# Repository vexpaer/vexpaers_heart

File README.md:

# vexpaer's heart — clean PCB rebuild

This branch resets the PCB layout workflow without losing the previous design.

- `Old/`: complete archived V1 design and production outputs.
- `reference/`: only the electrical/spec/library files needed for the rebuild.
- `hardware/heart_v2/`: clean workspace for the new PCB.
- `PCB_WORKFLOW.md`: the one document Codex should follow from setup to final manufacturing outputs.

The new PCB must be placement-first and human-routed. Do not use the archived PCB tracks or a global autorouter as the final layout.

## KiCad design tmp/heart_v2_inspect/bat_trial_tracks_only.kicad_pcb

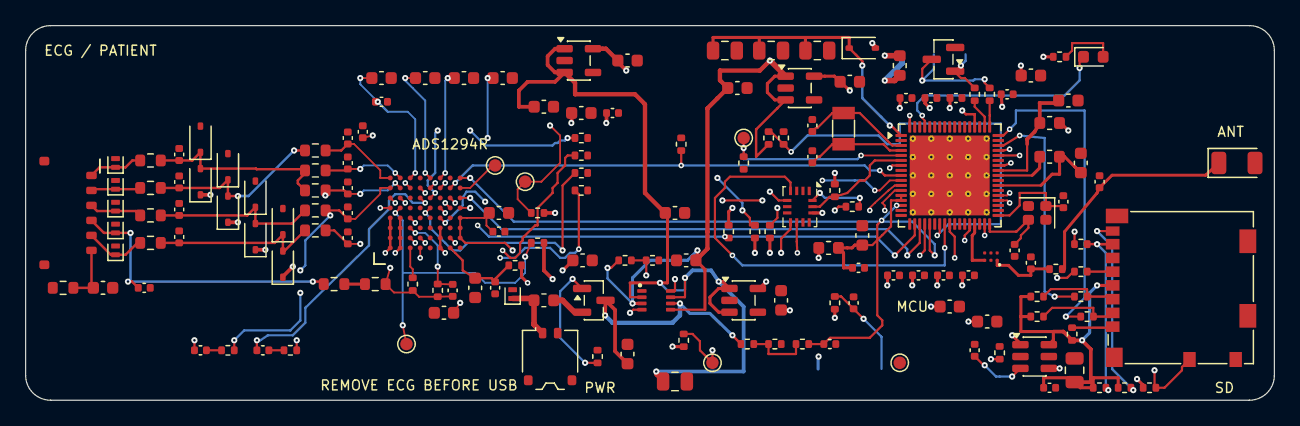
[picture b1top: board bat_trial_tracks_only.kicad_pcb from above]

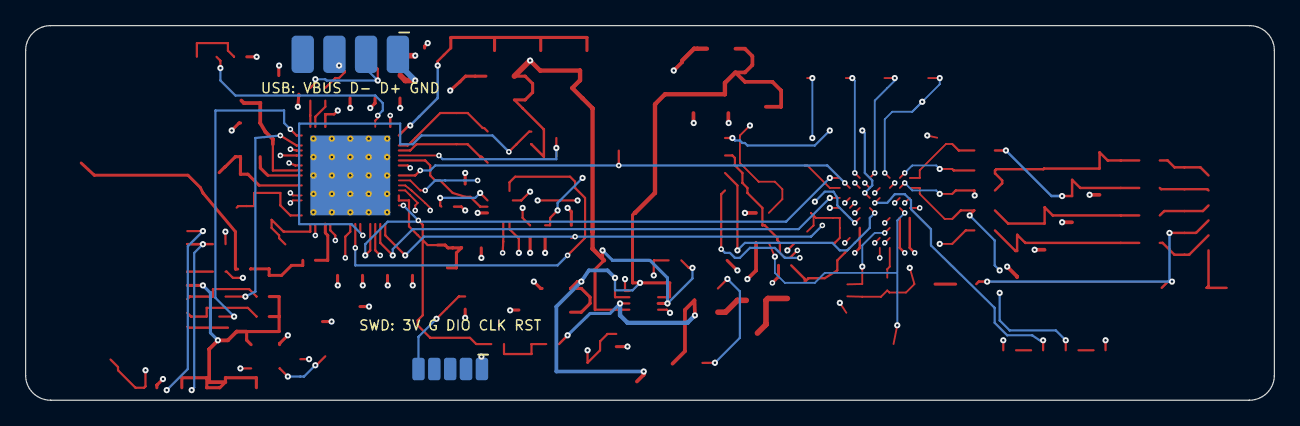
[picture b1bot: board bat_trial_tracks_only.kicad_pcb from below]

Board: 4 copper layers, 100.0 x 30.0 mm, 167 parts (2 on the bottom side), 102 nets.

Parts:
AE1: 2450AT18A100E; Johanson_2450AT18x100_2400-2500Mhz
C1, C2, C3, C4, C5, C6, C7, C8, C9, C13: 100p C0G; C_0402_1005Metric
C10: 100p C0G DNP; C_0402_1005Metric
C11: 1nF 100V C0G; C_0603_1608Metric
C12: 1.5nF C0G; C_0402_1005Metric
C14, C28, C33, C35: 10u 6.3V X5R; C_0603_1608Metric
C15, C21, C23, C25, C38, C48, C50, C51, C52, C53, C54, C55, C56, C58, C59, C64: 100n X7R; C_0402_1005Metric
C16: 22u 6.3V X5R; C_0603_1608Metric
C17, C18, C19, C20, C22, C24, C29, C30, C32, C34, C36, C49, C60, C62: 1u X7R; C_0603_1608Metric
C26, C27: 2.2n C0G DNP; C_0402_1005Metric
C31, C63: 22u 6.3V X5R; C_0805_2012Metric
C37, C46, C47, C57: 4.7u X7R; C_0603_1608Metric
C39, C40, C41: 47u 6.3V X5R; C_0805_2012Metric
C42, C43: 8.2p C0G; C_0402_1005Metric
C44, C45: 10p C0G; C_0402_1005Metric
C61: 1n X7R; C_0402_1005Metric
C65, C66: DNP; C_0402_1005Metric
D1, D2, D3, D4, D5, D14: PESD5V0U1UL; D_SOD-882
D6, D7, D8, D9, D10, D11, D12, D13: BAS116; D_SOD-323
D15: BAT54H; D_SOD-323
D16: GREEN 0603; LED_0603_1608Metric
F1, F2: 0.50A PTC; Fuse_0603_1608Metric
FB1: 600R@100MHz; L_0603_1608Metric
J1: ECG_HARNESS; Molex_Pico-EZmate_78171-5006
J2: PROTECTED_1S_LIPO; Molex_Pico-EZmate_78171-0002_1x02-1MP_P1.20mm_Vertical
J3: USB_POGO; Pogo_USB_4x1_P2.54_Bottom
J4: MICROSD; microSD_HC_Molex_104031-0811
J5: SWD_POGO; Pogo_SWD_5x1_P1.27_Bottom
L1: 10nH; L_0603_1608Metric
L2: 2.2uH; L_0603_1608Metric
Q1: DMP2035U; SOT-23
R1, R2, R3, R4, R5, R6, R7, R8, R9: 47.5k 0.1%; R_0603_1608Metric
R10, R11: 162k 0.1%; R_0603_1608Metric
R12: 1M; R_0603_1608Metric
R13, R15, R16, R17, R51, R52, R53, R54, R55: 0R; R_0402_1005Metric
R14, R20, R26: 1M; R_0402_1005Metric
R18, R19: 40.2k 0.1% DNP; R_0402_1005Metric
R21, R22, R41, R42, R43, R44: 22R; R_0402_1005Metric
R23: 300k; R_0402_1005Metric
R24, R25, R29, R30, R31, R32, R33, R34, R40, R50: 100k; R_0402_1005Metric
R27: 330k; R_0402_1005Metric
R28: 1k; R_0402_1005Metric
R35: 470k; R_0402_1005Metric
R36: 680k; R_0402_1005Metric
R37: 2.2k; R_0402_1005Metric
R38, R39: 4.7k; R_0402_1005Metric
R45, R46, R47, R48, R49: 47k; R_0402_1005Metric
TP1: CH4P; TestPoint_Pad_D1.0mm
TP2: CH4N; TestPoint_Pad_D1.0mm
TP3: BOOT0; TestPoint_Pad_D1.0mm
TP4: PWR_USB_N; TestPoint_Pad_D1.0mm
TP5: ADS_CLK; TestPoint_Pad_D1.0mm
TP6: SWO; TestPoint_Pad_D1.0mm
U1: ADS1294RIZXGT; ADS1294R_ZXG
U2: STM32WB55RGV6; QFN-68-1EP_8x8mm_P0.4mm_EP6.4x6.4mm_ThermalVias
U3: BMI270; Bosch_LGA-14_3x2.5mm_P0.5mm
U4: TPS2116DRLR; Texas_DRL0008A
U5: TPS7A2130PDBVR; SOT-23-5
U6: TPS7A2030PDBVR; SOT-23-5
U7: TPS7A2033PDBVR; SOT-23-5
U8: TPS22918DBVR; SOT-23-6
U9: MLPF-WB55-01E3
U10: TPD2EUSB30DRTR; SOT-23
Y1: 32MHz 6pF; Crystal_SMD_2016-4Pin_2.0x1.6mm
Y2: 32.768kHz 7pF; Crystal_SMD_3215-2Pin_3.2x1.5mm

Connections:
/3V0_A: C20.1, C21.1, C35.1, D6.1 (K), D8.1 (K), D10.1 (K), D12.1 (K), R15.1, R16.2, R17.2, U1.A1 (IN8P), U1.A2 (IN8N), U1.A4 (AVDD), U1.A6 (AVDD), U1.B1 (IN7P), U1.B2 (IN7N), U1.B4 (AVDD), U1.B6 (AVDD), U1.C1 (IN6P), U1.C2 (IN6N), U1.C6 (AVDD), U1.D1 (IN5P), U1.D2 (IN5N), U6.5 (OUT)
/3V0_D: C24.1, C25.1, C33.1, C51.1, C52.1, C53.1, C54.1, C55.1, C57.1, C58.1, C59.1, C60.1, C62.1, D15.2 (A), FB1.1, J5.1 (3V0_D), L1.1, R25.1, R29.1, R30.1, R32.1, R33.1, R37.1, R38.1, R39.1, R50.1, U1.B8 (CLKSEL), U1.C8 (DVDD), U1.D8 (DVDD), U2.30 (VDD), U2.33 (VDDRF), U2.45 (VDD), U2.68 (VDD), U3.5 (VDDIO), U3.8 (VDD), U3.12 (CSB), U5.5 (OUT), U8.1 (VIN)
/3V0_SD: C63.1, C64.1, J4.4 (VDD), R45.1, R46.1, R47.1, R48.1, R49.1, U8.6 (VOUT)
/3V3_USB: C37.1, C56.1, U2.55 (VDDUSB), U7.5 (OUT)
/ADS_AVDD1: C22.1, C23.1, R15.2, U1.A7 (AVDD1)
/ADS_CH1N: C2.1, R2.2, U1.H2 (IN1N)
/ADS_CH1P: C5.1, R5.2, U1.H1 (IN1P)
/ADS_CH2N: C3.1, R3.2, R19.2, U1.G2 (IN2N)
/ADS_CH2P: C7.1, R7.2, R18.2, U1.G1 (IN2P)
/ADS_CH3P: C9.1, R9.2, U1.F1 (IN3P)
/ADS_CH4N: R17.1, TP2.1 (1_1), U1.E2 (IN4N)
/ADS_CH4P: R16.1, TP1.1 (1_1), U1.E1 (IN4P)
/ADS_CLK: TP5.1 (1_1), U1.G8 (CLK)
/ADS_CS: R32.2, U1.F7 (CS), U2.19 (PA4)
/ADS_DRDY: U1.D6 (DRDY), U2.10 (PC1)
/ADS_GPIO1_TIE: R52.1, U1.F5 (GPIO1)
/ADS_GPIO2_TIE: R53.1, U1.E7 (GPIO2)
/ADS_GPIO3_TIE: R54.1, U1.E6 (GPIO3)
/ADS_GPIO4_TIE: R55.1, U1.E5 (GPIO4)
/ADS_MISO: U1.E8 (DOUT), U2.21 (PA6)
/ADS_MOSI: U1.H8 (DIN), U2.22 (PA7)
/ADS_PWDN: R29.2, U1.G5 (PWDN), U2.38 (PB0)
/ADS_RESET: R30.2, U1.G6 (RESET), U2.39 (PB1)
/ADS_RESP_MODN: C27.1, U1.F4 (RESP_MODN)
/ADS_RESP_MODP: C26.1, U1.G4 (RESP_MODP)
/ADS_RLDIN: R13.2, U1.A3 (RLDIN)
/ADS_RLDINV: C12.2, R14.2, U1.C3 (RLDINV)
/ADS_RLDOUT: C12.1, R10.1, R13.1, R14.1, U1.B3 (RLDOUT)
/ADS_SCLK: U1.F8 (SCLK), U2.20 (PA5)
/ADS_START: R31.1, U1.G7 (START), U2.9 (PC0)
/ADS_VCAP1: C16.1, U1.H5 (VCAP1)
/ADS_VCAP2: C17.1, U1.H6 (VCAP2)
/ADS_VCAP3: C18.1, U1.B7 (VCAP3)
/ADS_VCAP4: C19.1, U1.G3 (VCAP4)
/ADS_VREFP: C14.1, C15.1, U1.H3 (VREFP)
/ADS_WCT: C13.1, U1.D3 (WCT), U1.F2 (IN3N)
/BAT_ADC: C38.1, R28.2, U2.15 (PA0)
/BAT_FUSED: F1.2, Q1.2 (S)
/BAT_GATE: Q1.1 (G), R20.1
/BAT_PROT: C28.1, C30.1, Q1.3 (D), R26.1, U4.6 (VIN2)
/BAT_RAW: D14.1, F1.1, J2.1 (BAT+)
/BAT_SENSE_DIV: R26.2, R27.1, R28.1
/BOOT0: R34.1, TP3.1 (1_1), U2.5 (PH3-BOOT0)
/CABLE_SHIELD: C11.1, J1.6 (SHIELD), R12.1
/GND: C1.2, C2.2, C3.2, C4.2, C5.2, C6.2, C7.2, C8.2, C9.2, C10.2, C11.2, C13.2, C14.2, C15.2, C16.2, C17.2, C18.2, C19.2, C20.2, C21.2, C22.2, C23.2, C24.2, C25.2, C28.2, C29.2, C30.2, C31.2, C32.2, C33.2, C34.2, C35.2, C36.2, C37.2, C38.2, C39.2, C40.2, C41.2, C42.2, C43.2, C44.2, C45.2, C46.2, C47.2, C48.2, C49.2, C50.2, C51.2, C52.2, C53.2, C54.2, C55.2, C56.2, C57.2, C58.2, C59.2, C60.2, C61.2, C62.2, C63.2, C64.2, C65.2, C66.2, D1.2, D2.2, D3.2, D4.2, D5.2, D7.2 (A), D9.2 (A), D11.2 (A), D13.2 (A), D14.2, J2.2 (GND), J3.4 (GND), J4.6 (VSS), J4.10 (DET_B), J4.SH (SHIELD), J5.2 (GND), R12.2, R20.2, R24.2, R27.2, R31.2, R34.2, R36.2, R40.2, R52.2, R53.2, R54.2, R55.2, U1.A5 (AVSS), U1.A8 (AVSS1), U1.B5 (AVSS), U1.C5 (AVSS), U1.C7 (DGND), U1.D4 (AVSS), U1.D5 (AVSS), U1.D7 (DGND), U1.E4 (RESV1), U1.F6 (DAISY_IN), U1.H4 (VREFN), U1.H7 (DGND), U2.32 (VSSRF), U2.42 (VSSSMPS), U2.69 (VSS_EP), U3.1 (SDO/ADDR), U3.6 (GNDIO), U3.7 (GND), U4.1 (GND), U5.2 (GND), U6.2 (GND), U7.2 (GND), U8.2 (GND), U8.5 (QOD), U9.A2 (GND), U9.B1 (GND), U9.B2 (GND), U9.B3 (GND), U10.2 (GND), Y1.2 (GND1), Y1.4 (GND2)
/HSE_IN: C42.1, U2.35 (OSC_IN), Y1.1 (X1)
/HSE_OUT: C43.1, U2.34 (OSC_OUT), Y1.3 (X2)
/IMU_INT1: U2.25 (PC4), U3.4 (INT1)
/IMU_INT2: U2.26 (PC5), U3.9 (INT2)
/IMU_SCL: R38.2, U2.6 (PB8), U3.13 (SCx/SCL)
/IMU_SDA: R39.2, U2.7 (PB9), U3.14 (SDx/SDA)
/LA_ELEC: D2.1, J1.2 (LA), R4.1
/LA_PROT: C4.1, D8.2 (A), D9.1 (K), R4.2, R5.1
/LED_STATUS_A: D16.2 (A), R37.2
/LED_STATUS_N: D16.1 (K), U2.65 (PB5)
/LL_ELEC: D3.1, J1.3 (LL), R6.1
/LL_PROT: C6.1, D10.2 (A), D11.1 (K), R6.2, R7.1
/LSE_IN: C44.1, U2.3 (PC14-OSC32_IN), Y2.1 (X1)
/LSE_OUT: C45.1, U2.4 (PC15-OSC32_OUT), Y2.2 (X2)
/MCU_VDDA: C49.1, C50.1, FB1.2, U2.13 (VREF+), U2.14 (VDDA)
/MUX_PR1: R23.2, R24.1, U4.4 (PR1)
/NRST: C48.1, J5.5 (NRST), R33.2, U2.8 (NRST)
/PWR_USB_N: R25.2, TP4.1 (1_1), U4.8 (ST)
/RA_ELEC: D1.1, J1.1 (RA), R1.1
/RA_PROT: C1.1, D6.2 (A), D7.1 (K), R1.2, R2.1, R3.1
/RESP_N_AC: C27.2, R19.1
/RESP_P_AC: C26.2, R18.1
/RF_ANT_FEED: AE1.1 (FEED_1), C66.1, R51.2
/RF_FILTER_OUT: C65.1, R51.1, U9.A1 (OUT)
/RF_MCU: U2.31 (RF1), U9.A3 (IN)
/RLD_LIMIT_MID: R10.2, R11.1
/RL_ELEC: C10.1, D5.1, J1.4 (RL), R11.2
/RTC_HOLD: C39.1, C40.1, C41.1, D15.1 (K), U2.1 (VBAT)
/SD_CLK: J4.5 (CLK), R43.2
/SD_CMD: J4.3 (CMD/DI), R42.2, R47.2
/SD_CS_MCU: R41.1, U2.51 (PA10)
/SD_CT: C61.1, U8.3 (CT)
/SD_DAT0: J4.7 (DAT0/DO), R44.2, R48.2
/SD_DAT1: J4.8 (DAT1), R49.2
/SD_DAT2: J4.1 (DAT2), R45.2
/SD_DAT3: J4.2 (DAT3/CS), R41.2, R46.2
/SD_DETECT: J4.9 (DET_A), R50.2, U2.11 (PC2)
/SD_MISO_MCU: R44.1, U2.48 (PB14)
/SD_MOSI_MCU: R42.1, U2.49 (PB15)
/SD_PWR_EN: R40.1, U2.12 (PC3), U8.4 (ON)
/SD_SCK_MCU: R43.1, U2.47 (PB13)
/SMPS_FB: C47.1, L2.2, U2.41 (VFBSMPS)
/SMPS_IN: C46.1, L1.2, U2.44 (VDDSMPS)
/SMPS_SW: L2.1, U2.43 (VLXSMPS)
/SWCLK: J5.4 (SWCLK), U2.56 (PA14)
/SWDIO: J5.3 (SWDIO), U2.54 (PA13)
/SWO: TP6.1 (1_1), U2.63 (PB3)
/SYS_RAW: C31.1, C32.1, C34.1, U4.2 (VOUT), U4.7 (VOUT), U5.1 (IN), U5.3 (EN), U6.1 (IN), U6.3 (EN)
/USB_DM: R21.2, U2.52 (PA11)
/USB_DM_POGO: J3.2 (D-), R21.1, U10.3 (D-)
/USB_DP: R22.2, U2.53 (PA12)
/USB_DP_POGO: J3.3 (D+), R22.1, U10.1 (D+)
/USB_VBUS_SENSE: R35.2, R36.1, U2.24 (PA9)
/V5_ELEC: D4.1, J1.5 (V5), R8.1
/V5_PROT: C8.1, D12.2 (A), D13.1 (K), R8.2, R9.1
/VBUS: C29.1, C36.1, F2.2, R23.1, R35.1, U4.3 (VIN1), U4.5 (MODE), U7.1 (IN), U7.3 (EN)
/VBUS_RAW: F2.1, J3.1 (VBUS)

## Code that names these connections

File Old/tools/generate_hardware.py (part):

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        "H4": ("VREFN", "input"), "G4": ("RESP_MODP", "output"), "F4": ("RESP_MODN", "output"),
        "E4": ("RESV1", "input"), "D4": ("AVSS", "power_in"), "C4": ("RLDREF", "input"),
        "B4": ("AVDD", "power_in"), "A4": ("AVDD", "power_in"),
        "H5": ("VCAP1", "passive"), "G5": ("PWDN", "input"), "F5": ("GPIO1", "bidirectional"),
        "E5": ("GPIO4", "bidirectional"), "D5": ("AVSS", "power_in"), "C5": ("AVSS", "power_in"),
        "B5": ("AVSS", "power_in"), "A5": ("AVSS", "power_in"),
        "H6": ("VCAP2", "passive"), "G6": ("RESET", "input"), "F6": ("DAISY_IN", "input"),
        "E6": ("GPIO3", "bidirectional"), "D6": ("DRDY", "output"), "C6": ("AVDD", "power_in"),
        "B6": ("AVDD", "power_in"), "A6": ("AVDD", "power_in"),
        "H7": ("DGND", "power_in"), "G7": ("START", "input"), "F7": ("CS", "input"),
        "E7": ("GPIO2", "bidirectional"), "D7": ("DGND", "power_in"), "C7": ("DGND", "power_in"),
        "B7": ("VCAP3", "passive"), "A7": ("AVDD1", "power_in"),
        "H8": ("DIN", "input"), "G8": ("CLK", "bidirectional"), "F8": ("SCLK", "input"),
        "E8": ("DOUT", "output"), "D8": ("DVDD", "power_in"), "C8": ("DVDD", "power_in"),
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    )

    stm_names = {
        1:"VBAT",2:"PC13",3:"PC14-OSC32_IN",4:"PC15-OSC32_OUT",5:"PH3-BOOT0",6:"PB8",7:"PB9",8:"NRST",
        9:"PC0",10:"PC1",11:"PC2",12:"PC3",13:"VREF+",14:"VDDA",15:"PA0",16:"PA1",17:"PA2",18:"PA3",
        19:"PA4",20:"PA5",21:"PA6",22:"PA7",23:"PA8",24:"PA9",25:"PC4",26:"PC5",27:"PB2",28:"PB10",
        29:"PB11",30:"VDD",31:"RF1",32:"VSSRF",33:"VDDRF",34:"OSC_OUT",35:"OSC_IN",36:"AT0",37:"AT1",
        38:"PB0",39:"PB1",40:"PE4",41:"VFBSMPS",42:"VSSSMPS",43:"VLXSMPS",44:"VDDSMPS",45:"VDD",
        46:"PB12",47:"PB13",48:"PB14",49:"PB15",50:"PC6",51:"PA10",52:"PA11",53:"PA12",54:"PA13",
        55:"VDDUSB",56:"PA14",57:"PA15",58:"PC10",59:"PC11",60:"PC12",61:"PD0",62:"PD1",63:"PB3",
        64:"PB4",65:"PB5",66:"PB6",67:"PB7",68:"VDD",69:"VSS_EP",
    }
    power_names = {"VBAT", "VREF+", "VDDA", "VDD", "VSSRF", "VDDRF", "VSSSMPS", "VDDSMPS", "VDDUSB", "VSS_EP"}
    output_names = {"RF1", "OSC_OUT", "VLXSMPS"}
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        "D3":"ADS_WCT", "C3":"ADS_RLDINV", "B3":"ADS_RLDOUT", "A3":"ADS_RLDIN",
        "H4":"GND", "G4":"ADS_RESP_MODP", "F4":"ADS_RESP_MODN", "E4":"GND",
        "D4":"GND", "C4":None, "B4":"3V0_A", "A4":"3V0_A",
        "H5":"ADS_VCAP1", "G5":"ADS_PWDN", "F5":"ADS_GPIO1_TIE", "E5":"ADS_GPIO4_TIE",
        "D5":"GND", "C5":"GND", "B5":"GND", "A5":"GND",
        "H6":"ADS_VCAP2", "G6":"ADS_RESET", "F6":"GND", "E6":"ADS_GPIO3_TIE",
        "D6":"ADS_DRDY", "C6":"3V0_A", "B6":"3V0_A", "A6":"3V0_A",
        "H7":"GND", "G7":"ADS_START", "F7":"ADS_CS", "E7":"ADS_GPIO2_TIE",
        "D7":"GND", "C7":"GND", "B7":"ADS_VCAP3", "A7":"ADS_AVDD1",
        "H8":"ADS_MOSI", "G8":"ADS_CLK", "F8":"ADS_SCLK", "E8":"ADS_MISO",
        "D8":"3V0_D", "C8":"3V0_D", "B8":"3V0_D", "A8":"GND",
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    add_two(d, "R18", "40.2k 0.1% DNP", "R", "RESP_P_AC", "ADS_CH2P", 370, 160, dnp=True, manufacturer="Yageo", mpn="RT0402BRD0740K2L")
    add_two(d, "C27", "2.2n C0G DNP", "C", "ADS_RESP_MODN", "RESP_N_AC", 335, 176, dnp=True, manufacturer="Murata", mpn="GRM1555C1H222JA01D")
    add_two(d, "R19", "40.2k 0.1% DNP", "R", "RESP_N_AC", "ADS_CH2N", 370, 176, dnp=True, manufacturer="Yageo", mpn="RT0402BRD0740K2L")
    for ref, net, y in (("R52","ADS_GPIO1_TIE",190),("R53","ADS_GPIO2_TIE",202),("R54","ADS_GPIO3_TIE",214),("R55","ADS_GPIO4_TIE",226)):
        add_two(d, ref, "0R", "R", net, "GND", 385, y, manufacturer="Yageo", mpn="RC0402JR-070RL")

    # --------------------------------------------------------------- POWER IN
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    d.add("Y1", "32MHz 6pF", "XTAL4", footprint_for("XTAL4"), ["HSE_IN","GND","HSE_OUT","GND"], 425, 260, manufacturer="NDK", mpn="NX2016SA-32M-EXS00A-CS06465")
    add_two(d, "C42", "8.2p C0G", "C", "HSE_IN", "GND", 455, 252, manufacturer="Murata", mpn="GRM1555C1H8R2CA01D")
    add_two(d, "C43", "8.2p C0G", "C", "HSE_OUT", "GND", 455, 268, manufacturer="Murata", mpn="GRM1555C1H8R2CA01D")
    d.add("Y2", "32.768kHz 7pF", "XTAL2", "Crystal:Crystal_SMD_3215-2Pin_3.2x1.5mm", ["LSE_IN","LSE_OUT"], 510, 260, manufacturer="NDK", mpn="NX3215SA-32.768K-STD-MUA-14")
    add_two(d, "C44", "10p C0G", "C", "LSE_IN", "GND", 540, 252, manufacturer="Murata")
    add_two(d, "C45", "10p C0G", "C", "LSE_OUT", "GND", 540, 268, manufacturer="Murata")
    add_two(d, "L1", "10nH", "L", "3V0_D", "SMPS_IN", 570, 238, manufacturer="Murata", mpn="LQG15HN10NJ02D")
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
